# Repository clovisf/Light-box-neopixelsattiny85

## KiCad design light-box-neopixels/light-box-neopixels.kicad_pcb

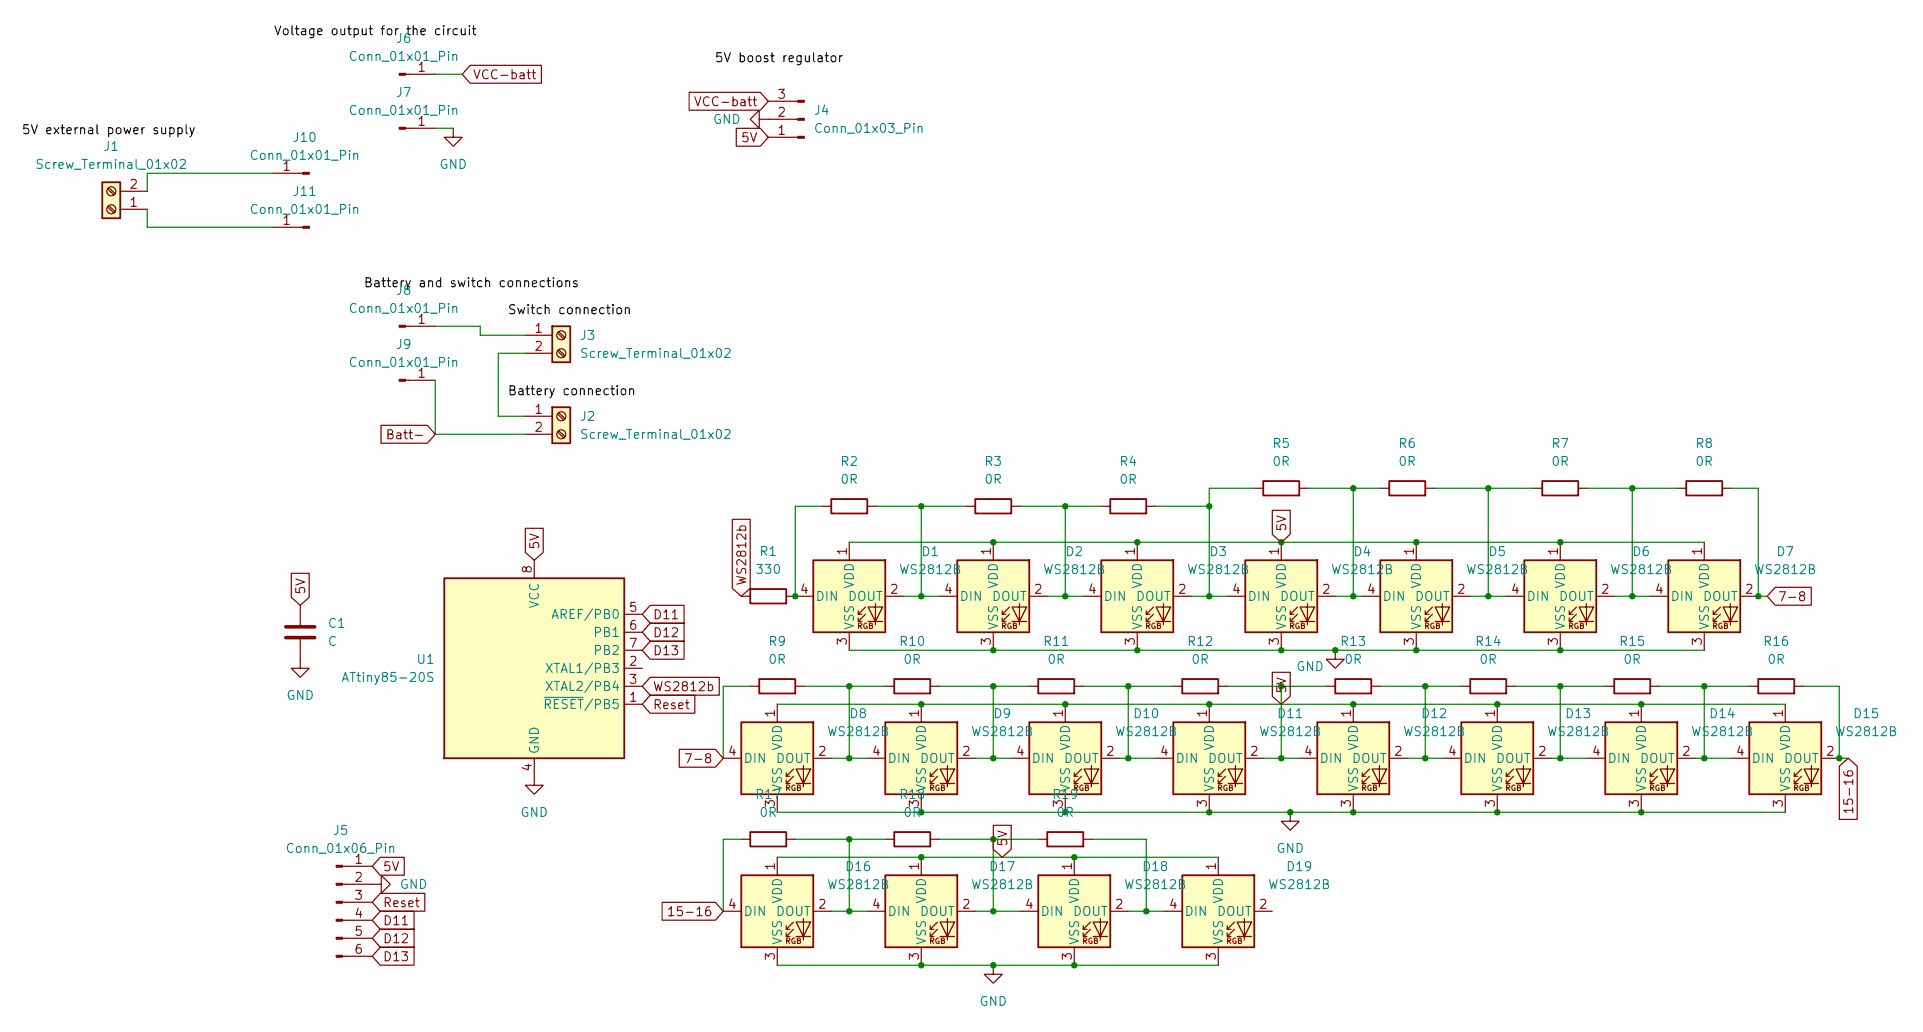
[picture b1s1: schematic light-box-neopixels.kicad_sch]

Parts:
C1: C; C_0805_2012Metric
D1, D2, D3, D4, D5, D6, D7, D8, D9, D10, D11, D12, D13, D14, D15, D16, D17, D18, D19: WS2812B; LED_WS2812B_PLCC4_5.0x5.0mm_P3.2mm
J1, J2, J3: Screw_Terminal_01x02; PhoenixContact_MSTBVA_2,5_2-G-5,08_1x02_P5.08mm_Vertical
J4: Conn_01x03_Pin; PinHeader_1x03_P2.54mm_Vertical
J5: Conn_01x06_Pin; PinHeader_1x06_P2.54mm_Vertical
J6, J7, J8, J9, J10, J11: Conn_01x01_Pin; PinHeader_1x01_P2.54mm_Vertical
R1: 330; R_0805_2012Metric
R2, R3, R4, R5, R6, R7, R8, R9, R10, R11, R12, R13, R14, R15, R16, R17, R18, R19: 0R; R_0805_2012Metric
U1: ATtiny85-20S; SOIC-8W_5.3x5.3mm_P1.27mm

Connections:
7-8: D7.2 (DOUT), D8.4 (DIN), R8.2, R9.1
15-16: D15.2 (DOUT), D16.4 (DIN), R16.2, R17.1
Batt-: J2.2, J9.1
D11: J5.4, U1.5 (AREF/PB0)
D12: J5.5, U1.6 (PB1)
D13: J5.6, U1.7 (PB2)
GND: C1.2, D1.3 (VSS), D2.3 (VSS), D3.3 (VSS), D4.3 (VSS), D5.3 (VSS), D6.3 (VSS), D7.3 (VSS), D8.3 (VSS), D9.3 (VSS), D10.3 (VSS), D11.3 (VSS), D12.3 (VSS), D13.3 (VSS), D14.3 (VSS), D15.3 (VSS), D16.3 (VSS), D17.3 (VSS), D18.3 (VSS), D19.3 (VSS), J4.2, J5.2, J7.1, U1.4 (GND)
unnamed: D1.4 (DIN), R1.2, R2.1
unnamed: D1.2 (DOUT), D2.4 (DIN), R2.2, R3.1
unnamed: D2.2 (DOUT), D3.4 (DIN), R3.2, R4.1
unnamed: D3.2 (DOUT), D4.4 (DIN), R4.2, R5.1
unnamed: D4.2 (DOUT), D5.4 (DIN), R5.2, R6.1
unnamed: D5.2 (DOUT), D6.4 (DIN), R6.2, R7.1
unnamed: D6.2 (DOUT), D7.4 (DIN), R7.2, R8.1
unnamed: D8.2 (DOUT), D9.4 (DIN), R9.2, R10.1
unnamed: D9.2 (DOUT), D10.4 (DIN), R10.2, R11.1
unnamed: D10.2 (DOUT), D11.4 (DIN), R11.2, R12.1
unnamed: D12.2 (DOUT), D13.4 (DIN), R13.2, R14.1
unnamed: D13.2 (DOUT), D14.4 (DIN), R14.2, R15.1
unnamed: D14.2 (DOUT), D15.4 (DIN), R15.2, R16.1
unnamed: D16.2 (DOUT), D17.4 (DIN), R17.2, R18.1
unnamed: D17.2 (DOUT), D18.4 (DIN), R18.2, R19.1
unnamed: D18.2 (DOUT), D19.4 (DIN), R19.2
unnamed: J1.1, J11.1
unnamed: J1.2, J10.1
unnamed: J2.1, J3.2
unnamed: J3.1, J8.1
Reset: J5.3, U1.1 (~RESET/PB5)
VCC-batt: J4.3, J6.1
WS2812b: R1.1, U1.3 (XTAL2/PB4)

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
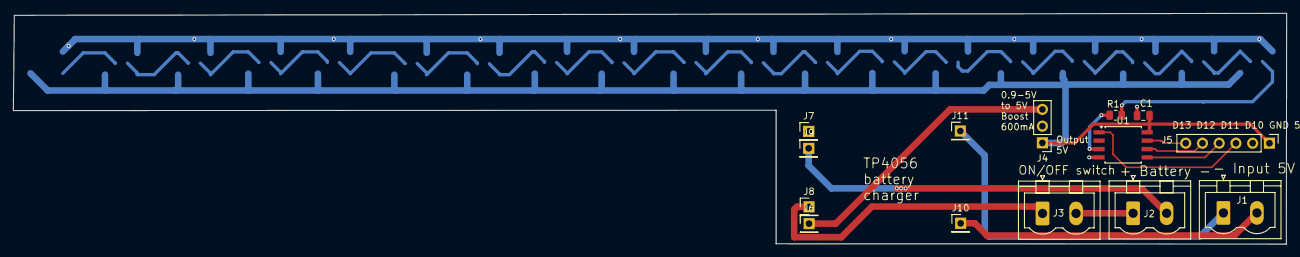
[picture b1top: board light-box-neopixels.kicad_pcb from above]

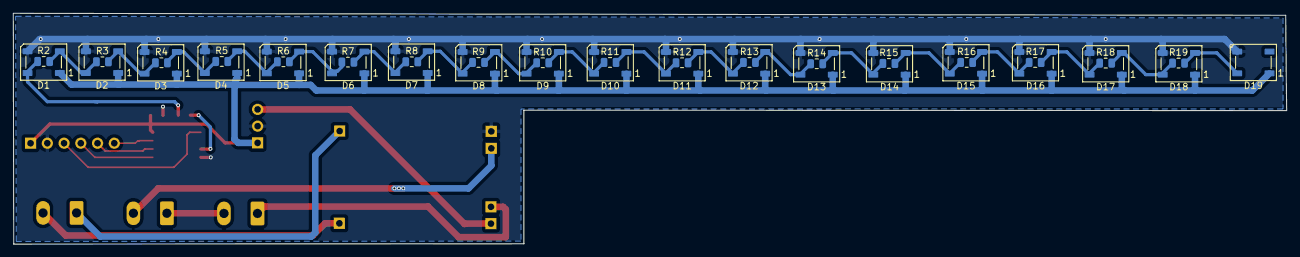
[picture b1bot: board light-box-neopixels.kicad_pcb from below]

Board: 2 copper layers, 193.2 x 35.0 mm, 51 parts (37 on the bottom side), 32 nets.

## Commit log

2024-10-20 Generated Gerber files
2024-10-20 Added code used in the product
2024-10-21 backups
